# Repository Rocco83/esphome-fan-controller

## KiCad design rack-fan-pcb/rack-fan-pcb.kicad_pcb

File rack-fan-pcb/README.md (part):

# Rack fan controller board

Controller board for the rack's 19" fan tray: six 4-pin PWM fans, up to eight DS18B20 probes, wired Ethernet. KiCad 10 project, through-hole parts only, **manufactured PCB** (it started as a perfboard design).

- Firmware: [`../rack-fan.yaml`](../rack-fan.yaml) + [`../rack-fan-channel.yaml`](../rack-fan-channel.yaml)
- Project overview, fan choice and control logic: [`../README-rack-fan.md`](../README-rack-fan.md)
- This file: every decision taken for the board, why, and what the alternatives were.

## Contents

- [Summary](#summary)
- [Decisions](#decisions)
- [Pin assignment](#pin-assignment)
- [Board layout](#board-layout)
- [Parts](#parts)
- [Library sources](#library-sources)
- [Firmware coupling](#firmware-coupling)
- [Verification status](#verification-status)
- [Open items](#open-items)
- [Sources](#sources)

## Summary

| Area | Decision |
|---|---|
| Controller | WT32-ETH01 (ESP32 + LAN8720), **mounted face down** in two 1 × 12 female sockets |
| Fans | 6 channels (Noctua NF-F12 industrialPPC-24V-3000 planned), each with its own PWM and tach |
| PWM stage | 2N3904 open collector per fan: 4.7 kΩ base, 100 kΩ pull-down, inverting |
| Tach | Direct to a GPIO per fan, 10 kΩ pull-up to 3.3 V, hardware pulse counter |
| Probes | DS18B20 on two 1-Wire buses (GPIO5, GPIO17), 4 JST XH connectors per bus |
| Power in | 24 V, Mean Well GST90A24-P1M (5.5/2.5 jack J5), or an XLG LED driver on J1 |
| Protection | 5×20 T2A fuse (PTF78 holder), 1N5822 reverse-polarity diode, 470 µF bulk |
| Logic supply | Traco TSR 1-2450 (24 V → 5 V) into the WT32's 5V pin; 3.3 V from the WT32 |
| Boot robustness | C3 470 µF on EN; fans fail to 100% (except FAN1, see pin 26) |
| Board | Manufactured PCB, outline drawn by the user on Edge.Cuts (≈ 66.5 × 87 mm), parts on a 0.635 mm grid |
| Grounding | Star ground at the power input; logic ground enters the WT32 through **one** GND pin (WT32 GND and 3V3 pins declared as jumper groups) |
| Mounting | 4 × M3 holes (MountingHole_3.2mm_M3), 4 mm in from the corners, **not connected** |

## Decisions

### 1. Controller: WT32-ETH01, socketed, face down

- **Wired Ethernet** for a rack device: no Wi-Fi dependency.
- **Sockets:** the module plugs into two 1 × 12 female headers, so it can be removed to flash it over serial.
- **Pins 13 (LINK) and 14 (GND) have no socket.** They are the pair at the RJ45 end, and with the RJ45 overhanging the board they fall ~0.5 mm past the edge. The edge can't move out to include them: face down, the RJ45 body must clear the board, and it starts only ~1.7 mm beyond the edge. LINK was unused and pin 14 is one of five GND pins, so nothing is lost. The module's two pins simply hang beside the edge. The pads are removed from the footprint and the pins from the symbol; the other pins keep their numbers.
- **Face down:** the module sits components-towards-the-board. That mirrors its two pin rows, so the project uses its own footprint `rack-fan:WT32-ETH01_Socket_FaceDown`. The RJ45 overhangs the left board edge.
- **Row spacing:** 22.86 mm (9 holes), cross-checked against an independent KiCad footprint ([egnor/wt32-eth01](https://github.com/egnor/wt32-eth01)). Measure the module with calipers before soldering the sockets.
- **Pins left:** Ethernet takes GPIO0, 16, 18, 19, 21, 22, 23, 25, 26 and 27. Only 14 GPIOs remain on the header: 1, 2, 3, 4, 5, 12, 14, 15, 17, 32, 33, 35, 36, 39. That budget drives most of the decisions below.

### 2. Six fans, not eight

- 6 PWM + 6 tach + 2 probe buses use all 14 pins.
- **8 fans would need a tach multiplexer.** A 74HC4052 reads one fan at a time, so RPM would update only every ~10 s. Rejected: instant tach readings were preferred.
- **Other ways to 8 fans, both rejected:**
  - a second microcontroller counting the tachs and reporting over I2C
  - an I2C fan-controller chip (MAX31790, EMC2305), which is surface-mount and has no ESPHome support
- **PCA9685 (on hand): rejected.** Its PWM tops out at 1526 Hz (about 3 kHz with an external clock), and the fans need 21–28 kHz. Its I2C also costs 2 pins, and the PW package is surface-mount.

### 3. PWM stage: 2N3904 open collector

```
GPIO ──┬──[4.7 kΩ]── 2N3904 base           fan's internal pull-up
       │             collector ─────────────────┴── fan PWM wire (pin 4)
   [100 kΩ]          emitter ── GND
       │
      GND
```

Why it's needed:
- **Levels:** the fan pulls its PWM wire up to as much as 5 V, above the ESP32's 3.3 V rating, and 3.3 V does not reach the 4.75 V high threshold of some fans (San Ace).

Why this circuit:
- **Drive:** 3.3 V through 4.7 kΩ gives about 0.56 mA of base current. That saturates the transistor at 0.1–0.2 V for the ≤ 5 mA a fan input sinks, guaranteed at 3.3 V. At 25 kHz, turn-off delay costs about 1% of duty.
- **Inverting:** the firmware sets `inverted: true`, so the output level equals the fan duty.
- **Fail-safe:** GPIO low, floating or unpowered means the transistor is off, the wire floats high, and the fan runs at 100%.
- **Strapping pins:** the 100 kΩ pull-down keeps GPIO2 and GPIO12 low at boot.

Alternatives rejected:

| Alternative | Why not |
|---|---|
| 2N7000 MOSFET | Worst-case gate threshold 3 V, too close to the 3.3 V drive |
| 74LVC06A (open-drain inverter) | Surface-mount only |
| BSS138 level-shifter module | Its 3.3 V-side pull-up holds GPIO2/GPIO12 high at boot (GPIO12 high = no boot) |
| 74AHCT125 5 V buffer | Non-inverting: a dead GPIO stops the fan |
| TXB0108 / TXS0108 | Auto-direction shifters misbehave with the fans' pull-ups |
| ULN2003 / ULN2803 | Darlington saturation ~0.9 V, above the 0.4 V low threshold of some fans |
| Direct GPIO | Over-voltage on the pin; insufficient high level |
| 4.7 kΩ pull-downs on pins with a reset pull-up | Would make those fans fail-safe at boot, but rejected: no resistor value changes. Fixed instead by choosing which pins carry PWM (see pin assignment) |

### 4. Tach inputs: direct, one GPIO per fan

- **Circuit:** open collector, 2 pulses per revolution, one 10 kΩ pull-up per fan to **3.3 V** (never 5 V). The pull-up is required on GPIO35/36/39, which have no internal pull-up.
- **Counting:** a hardware pulse counter per fan (6 of the ESP32's 8), live RPM.
- **Filter:** `internal_filter: 13us` (the hardware maximum, 12.8 µs). It also removes the ~80 ns low glitches that ESP32 erratum GPIO-3.11 puts on GPIO36/39 when the ADC powers on. The firmware doesn't use the ADC; the filter is a safeguard.
- **Not on the module's LED pins:** the WT32 has LEDs on GPIO5 and GPIO17. As a tach input, the LED path would add up to ~1.5 mA, against the Noctua's 2 mA tach rating.

### 5. Temperature probes: DS18B20 on two 1-Wire buses

- **DS18B20 chosen over NTC (both on hand):**
  - NTCs need analog inputs, and the ADC1 pins (32/33/35/36/39) are all used.
  - An I2C ADC (ADS1115) would need 2 more pins.
  - The I2C multiplexer (also on hand) was for SHT21 probes sharing one address; DS18B20s share a bus without it.
- **Two buses, 4 connectors each, odd/even:** J21–J24 are TEMP1, 3, 5, 7 (bus A, ONEWIRE_A) and J25–J28 are TEMP2, 4, 6, 8 (bus B, ONEWIRE_B). The hot zone has probes on both buses, so a bus fault (crushed cable, shorted probe) still leaves a hot-zone reading; it also keeps each star of cables short.
  - Bus A: TEMP1 Rear High, TEMP3 Rear Low, TEMP5 Front Low, TEMP7 Inlet.
  - Bus B: TEMP2 Rear Mid, TEMP4 Front High, TEMP6 Outlet, TEMP8 Other Room.
- **Pins GPIO5 and GPIO17:** the module's LED3/LED4 sit there (3V3 → LED → 1 kΩ → pin). For 1-Wire that's harmless: about 1.3 mA of extra pull-up, well within the DS18B20's 4 mA sink, and the LEDs blink with traffic. Those pins were bad for PWM and tach, so 1-Wire is their best use.
- **Pull-up:** 4.7 kΩ per bus (R31, R32); use 2.2 kΩ for long cables.
- **Connectors:** JST XH 3-pin vertical (B3B-XH-A), pin order 1 GND, 2 DQ, 3 VDD.
  - 5.08 mm screw terminals were the first choice but **did not fit**: four in a row need ~17 holes plus spacing, and only ~18 were free beside the fan resistors.
  - XH needs a crimped plug on each probe cable.
- **Probes and names:** eight probes, named after their connector: TEMP1 Rear High, TEMP2 Rear Mid, TEMP3 Rear Low, TEMP4 Front High, TEMP5 Front Low, TEMP6 Outlet, TEMP7 Inlet, TEMP8 Other Room. Cables: 5 m on TEMP4, 6 and 8, 2 m on the others. ESPHome shows them as `Rack Fan TEMP1 Rear High` … `Rack Fan TEMP8 Other Room`. Each name is bound to a probe address in the firmware, so each probe must go into the connector of its name.

### 6. Power

**Input supply: Mean Well GST90A24-P1M** (24 V, 3.75 A, 90 W desktop adapter).
- True constant-voltage supply, and **no mains wiring** on the project at all.
- The **P1M plug is 5.5/2.5 mm, centre positive** (Mean Well datasheet), so J5 must be a **2.5 mm-pin** barrel jack. The common DC-005 jack comes in both pin sizes with the same body, so the footprint fits either.
- **No jack takes both 2.1 and 2.5 reliably.** A 2.1 pin accepts a 2.5 plug but with loose contact, which isn't acceptable at ~26 W. A 2.5 pin doesn't accept a 2.1 plug.
- In Italy, generic adapters are more often 5.5/2.1. If that's preferred, use the GST90A24-P1J with a 2.1 jack.
- **Alternatives:** Mean Well XLG-100-24-A or XLG-75-24-A LED drivers on **J1** (5.08 mm screw terminal). Below their current setting they act as a 24 V supply; leave the potentiometer at maximum. Their flying mains leads need an earthed enclosure wired by someone qualified. Fit J1 **or** J5, not both.

**Load:** 6 × 4.32 W ≈ 26 W (1.1 A) for the fans, plus ~1.5 W of logic.

On the board:

| Ref | Part | Why |
|---|---|---|
| F1 | 5×20 fuse **T2A** (slow-blow) in a Stelvio-Kontek PTF78 holder | Protects the wiring on a short. The footprint is the same one used in espfreezanz. It replaced an earlier resettable PTC fuse |
| D1 | 1N5822 Schottky (3 A) | Reverse polarity. Drops ~0.5 V, so the fans see ~23.5 V |
| C1 | 470 µF 35 V | Bulk capacitance on the fan rail: fan start-up and PWM current pulses |
| U2 | Traco TSR 1-2450 | 24 V → 5 V, 1 A, input 6.5–36 V, fixed output. Preferred to an LM2596 module, which is adjustable and can be set wrong, and has no grid-friendly footprint |
| C2 | 47 µF 10 V | TSR output capacitor |
| C3 | 470 µF 10 V on **EN** | Boot robustness, see below |

**3.3 V** for the pull-ups and probes comes from the WT32's own regulator (pin 10), well under 50 mA.

**C3 on EN, and why not a bigger capacitor on 24 V instead:**
- Some WT32-ETH01 boards hang at power-up when the supply ramps slowly. The ESP32 leaves reset while its 3.3 V is still rising (adapter → TSR → module regulator).
- A capacitor on EN holds the ESP32 in reset until the supply has settled. 470 µF is the value users reported fixing it, with ~1.5–2 s of extra boot delay ([WLED forum](https://wled.discourse.group/t/wt32-eth01-hangs-on-boot-after-psu-power-up/2937)).
- A bigger capacitor on the 24 V line would make the ramp **slower**, the condition that causes the hang. C1 stays for the fan rail; C3 is a different job.
- A smaller C3 (e.g. 100 µF) fits the same footprint and boots faster, but nobody has reported testing it.

### 7. Board type: manufactured PCB

The board started as a perfboard layout (Eurocard, everything on the 2.54 mm hole grid). It is now a **manufactured PCB**:
- The outline is the rectangle the user drew on Edge.Cuts, about 66.5 × 87 mm.
- Parts sit on a 0.635 mm (25 mil) placement grid instead of the 2.54 mm hole grid. That allows the tighter resistor packing and channel pitch below.

### 8. Grounding: star ground, one WT32 GND pin

- **The concern:** the WT32's five GND pins (2, 9, 11, 14, 23; 14 is not fitted) are all tied to the module's internal ground plane. Linking them again on the board only adds a small parallel path, which is harmless in itself. The real risk is the **fan return current** (up to ~1.1 A, pulsed at 25 kHz) entering the module at one GND pin and leaving at another. The ESP32 and the Ethernet PHY would then sit on a bouncing ground.
- **Decision: star ground** at the power input (J5/J1, C1):
  - **Power branch:** fan returns (J11–J16 pin 1), the 2N3904 emitters and the 100 kΩ pull-downs go straight to the star point.
  - **Logic branch:** WT32, TSR 1-2450 ground, C2, C3, the probe GND and R31/R32 go to the star point as their own branch. That branch enters the module through **one** GND pin.
  - Fan current then never crosses the module.
- **How KiCad accepts it:** the WT32 symbol and footprint declare **jumper groups**: GND (2, 9, 11, 23), 3V3 (3, 10). EN (1, 4) was a group too, but KiCad 10's *Update PCB from Schematic* then split the EN net in two (`/EN` on pin 1, `/EN_1` on pin 4 and its tracks), so it was removed: pin 1 carries a no-connect flag and pin 4 is the routed EN pin. The module ties them internally.
  - KiCad 9/10 then treats each group as connected inside the part, so routing one pin per group satisfies the ratsnest and DRC.
  - Tokens: `jumper_pin_groups` in the symbol, `jumper_pad_groups` in the footprint, as written by KiCad's own file formatter.
  - KiCad 10.0.4 bug #25063 affects only pins defined as a list, not this part.
- **Which GND pin:** route the logic branch to the WT32 GND pin nearest the 5V/3V3 pins (pin 9 or 11), so the module's supply and its return are next to each other.

### 9. Mounting holes

- **What:** 4 × stock `MountingHole:MountingHole_3.2mm_M3` (same footprint as espfreezanz), centres 4 mm in from each corner of the outline.
- **Not connected, deliberately.** Metal holes tied to GND would make the chassis a second ground path, a real ground loop.
- **No schematic symbol:** they are board-only footprints (H1–H4).

### 10. Serial

- UART0 (GPIO1/GPIO3) carries FAN1's PWM and tach, so **there is no serial console at runtime**. Logs come over the API and the web server.
- **Flashing:** over the network after the first flash. For a serial flash (first flash, or recovery) use the three headers below, or take the module out of its sockets.
- **J2 UART** (1 × 3, 2.54 mm): 1 GND, 2 RX = IO3/RXD0 (net TACH1), 3 TX = IO1/TXD0 (net PWM1). Labels are from the ESP32's side: the adapter's TX goes to pin 2, its RX to pin 3. Use a **3.3 V** adapter and **unplug FAN1** first, since its tach would drive RX. The PWM1 stage (4.7 kΩ into Q1's base, 100 kΩ pull-down) only loads TX lightly.
- **J3 RESET** (1 × 3): 1 EN, 2 GND, 3 not connected. A jumper on 1-2 holds the ESP32 in reset; pin 3 is the parking place (jumper on 2-3). Shorting EN also discharges C3 (470 µF) through the jumper, which is harmless at 3.3 V.
- **J4 BOOT** (1 × 3): 1 IO0, 2 GND, 3 not connected. Jumper on 1-2 at power-on (or while releasing RESET) = serial download mode; park it on 2-3 for normal use.
- **IO0 is the Ethernet 50 MHz clock input.** The track to J4 is a stub on that clock: keep it **as short as possible**, J4 right next to U1 pin 24, and never leave the BOOT jumper on in normal use. A long IO0 track can break Ethernet.
- **Flash procedure:** FAN1 unplugged, adapter on J2, BOOT jumper on 1-2, power on (or RESET jumper on 1-2 and off), flash, BOOT jumper back to 2-3, reset.
- **Placement:** J2–J4 were added outside the board outline (right side), with nets assigned; place and route them by hand.

## Pin assignment

### Rules that decide every pin

From the [ESP32 datasheet](https://www.espressif.com/sites/default/files/documentation/esp32_datasheet_en.pdf) (strapping pins, IO_MUX reset states) and the [WT32-ETH01 V1.4 schematic](https://github.com/egnor/wt32-eth01):

**Must-haves:**
- **GPIO12 (MTDI)** must be low at boot, or the flash gets 1.8 V and the board won't boot. It can only carry a pulled-down PWM.
- **GPIO2** must be low or floating to enter serial download mode. It can only carry a pulled-down PWM.
- **GPIO35/36/39** are input-only with no pull resistors, so they can only be tachs.
- **GPIO1 (U0TXD)** carries the ROM boot message and is pulled up at reset. It can't be a tach (driven at boot).
- **GPIO0** is the Ethernet clock: unusable.

**What makes a pin good or bad for a job:**
- **PWM is only fail-safe** on pins that are low or floating during reset: GPIO2, GPIO4, GPIO12 (internal pull-down) and GPIO32, GPIO33 (no pull). That's only **5 pins for 6 PWMs**. The 6th PWM necessarily sits on a pin that switches its fan off during reset and boot.
- **Pins with an internal pull-up at reset:** GPIO3, GPIO5, GPIO14, GPIO15 (and GPIO1). Harmless for a tach or 1-Wire; for PWM, the fan stops while the ESP32 is in reset.
- **Module LED pins (GPIO5, GPIO17):** good for 1-Wire. Tight for a tach (current), not fail-safe for PWM.
- **Routing:** the face-down mount swaps the rows. Assignments were chosen to keep each signal on the row nearest its destination, to avoid crossings between the two rows.

### Final assignment

Pins 14–26 are one header row, 1–13 the other. "Pin" is the WT32 header pin, which is also the footprint pad.

| Pin | GPIO | Function | Why this pin | Alternatives for this pin | Caveat |
|---|---|---|---|---|---|
| 26 | IO1 | **PWM1** | Closest pin to FAN1. It couldn't be a tach, and moving 1-Wire to the LED pins freed it | 1-Wire. Not a tach | FAN1 stops for ~1 s at each boot/OTA reboot (reset pull-up, ROM message, then idle high until `on_boot` sets 100%), and stays stopped if the ESP32 is stuck rebooting or held in reset. Accepted: the 6th PWM has to be on such a pin |
| 25 | IO3 | **TACH1** | Pull-up at reset = tach idle level. RX is unused at runtime | PWM (fan would stop during reset), 1-Wire | None |
| 24 | IO0 | **BOOT (J4)** | Ethernet clock input; strapping pin (low = download mode) | — | Only a very short track to J4 |
| 23 | — | GND | | | |
| 22 | IO39 | **TACH2** | Input-only: tach is the only use | Another tach only | Erratum GPIO-3.11 glitch removed by the filter |
| 21 | IO36 | **TACH3** | Input-only: tach is the only use | Another tach only | Erratum GPIO-3.11 glitch removed by the filter |
| 20 | IO15 | **TACH4** | Strapping pin (boot log) whose default is high; the tach pull-up keeps it there | 1-Wire. PWM would stop its fan during reset (pull-up) and silence the boot log | Hobby sources claim a short pulse burst at boot; Espressif documents output disabled (see open items) |
| 19 | IO14 | **TACH5** | Pull-up after reset = tach idle level | 1-Wire. PWM would stop its fan during reset | Same undocumented boot-burst claim |
| 18 | IO12 | **PWM2** | Must stay low at boot: only a pulled-down PWM qualifies | Another PWM only. Never a tach or 1-Wire (pull-up → no boot) | None while the 100 kΩ pull-down is fitted |
| 17 | IO35 | **TACH6** | Input-only: tach is the only use | Another tach only | None |
| 16 | IO4 | **PWM3** | Pull-down at reset: fail-safe PWM | Tach, 1-Wire | None |
| 15 | IO2 | **PWM4** | Must stay low/floating for serial download: only a pulled-down PWM qualifies. Pull-down at reset: fail-safe | Another PWM only. Never a tach or 1-Wire | None |
| 14 | — | GND (no socket) | | | Past the board edge, not fitted |
| 1 | EN | — | Same signal as pin 4 | | Unconnected |
| 2 | — | GND | | | |
| 3 | 3V3 | — | Same rail as pin 10 | | Unconnected |
| 4 | EN | **EN** | C3 to GND | | Adds ~1.5–2 s of boot delay |
| 5 | IO32 | **PWM6** | No pull at reset: fail-safe PWM | Tach, 1-Wire | None (v2: swapped with PWM5 for routing) |
| 6 | IO33 | **PWM5** | No pull at reset: fail-safe PWM | Tach, 1-Wire | None (v2: swapped with PWM6 for routing) |
| 7 | IO5 | **ONEWIRE_A** | Module LED3: the best use is 1-Wire. Strapping pin whose default is high, kept by the bus pull-up | Tach (tight: LED current against the 2 mA tach rating). PWM would stop its fan during reset (pull-up + LED) | LED3 blinks with bus traffic |
| 8 | IO17 | **ONEWIRE_B** | Module LED4: the best use is 1-Wire | Tach (tight, as above). PWM would stop its fan during reset (LED pull-up) | LED4 blinks with bus traffic |
| 9 | — | GND | | | |
| 10 | 3V3 | **3.3V** | Supply for pull-ups and probes | | < 50 mA |
| 11 | — | GND | | | |
| 12 | 5V | **+5V** | From U2 (TSR 1-2450) | | |
| 13 | LINK | — (no socket) | | | Past the board edge, not fitted |

Result:
- Every fan except FAN1 runs at 100% from power-on until the firmware takes over, and if the ESP32 is in reset.
- There's no strapping conflict.
- The module LEDs only blink on the probe buses.

**How the assignment evolved**, for the record:
1. **First pass:** probe buses on GPIO1/GPIO3, tachs partly on GPIO5/GPIO17.
2. **Second pass:** after the module was turned face down, the assignment was rearranged for routing. FAN5/FAN6 went to the short row, and each fan's PWM and tach went on the row nearest its connector.
3. **Final:** the reset-state analysis and the WT32 schematic (LEDs on GPIO5/GPIO17) moved 1-Wire to the LED pins and the pull-up pins (IO3, IO14, IO15) to tachs. That left only the unavoidable 6th PWM on GPIO1, which is closest to FAN1. A swap of ONEWIRE_B onto GPIO14 was considered and dropped, because it moved signals between rows.

## Board layout

- **Outline:** the user's Edge.Cuts rectangle (≈ 66.5 × 87 mm).
  - The fan headers sit on the right edge.
  - The RJ45 overhangs the left edge on purpose.
  - The barrel jack J5 extends past the top edge (see open items).
- **Grid:** 0.635 mm (25 mil) placement grid. The part's pin 1 is on the grid; pins with their own pitch (XH 2.50 mm, fuse holder 22.6 mm, C1 5.00 mm) follow from it.
- **Fan channels:** one column, **FAN1 at the top of the board**, pitch **11.43 mm**. The fan header's housing is 11.1 mm, so they don't touch. Every channel copies the user-defined channel-6 pattern, aligned:
  - **fan header** (pad 1 at the top: GND, +24V, TACH, PWM)
  - **2N3904** to its left, its **bottom pin (collector) level with the fan header's bottom pin (PWM)**
  - **three resistors packed together** to the left, rows **3.175 mm** apart (0207 courtyard 3.0 mm, so no overlaps), the bottom row level with the fan header's bottom pin:
    - 100 kΩ pull-down (top)
    - 4.7 kΩ base (middle)
    - 10 kΩ tach pull-up (bottom)
  - the three resistors share one column (pad 1 x), the transistors another, the fan headers another
- **TEMP1–TEMP8 (JST XH):** two rows of four at equal spacing (9.525 mm), rows 12.07 mm apart, bottom-left.
- **R32, R31, C3:** one row under the WT32. C3 sits just clear of the module outline.
- **Power:** top-left (J1/J5, F1, D1, C1, U2, C2), snapped to the grid without changing the user's arrangement.
- **Silkscreen:**
  - connectors show their function: FAN1–FAN6, TEMP1–TEMP8, 24V IN
  - **back silkscreen (B.SilkS, mirrored):**
    - **the value of every part:** resistors, capacitors, Q1–Q6 (2N3904), D1, U1, U2 and F1. For F1 and the connectors, whose value is printed on the front, it's a board text copy, so their footprints still match the library.
    - **the use of every connector pin:** FAN1–FAN6 GND / +24V / TACH / PWM; TEMP1–TEMP8 GND / DQ / 3V3; J1 + / GND.
    - checked: no back text overlaps another, a pad or the board edge
    - pin labels are 0.7 mm high, values 0.8 mm. The board's minimum text height rule is set to **0.7 mm** to match (it was 0.8 mm). Check that your fab accepts 0.7 mm silkscreen text; if not, enlarge the pin labels instead.
  - reference designators are on the fabrication layer
  - "LOW" (above FAN1) and "HIGH" (below FAN6) mark the zones, so the tray is mounted with FAN1 at the bottom
- **Tracks:** routed by the user (238 segments, both layers). KiCad 10 DRC: no errors, warnings only.
- **Net classes** (project file):

  | Class | Nets | Track | Clearance | Why |
  |---|---|---|---|---|
  | Power | +24V, GND, VIN_RAW, VIN_FUSED | 1.0 mm | 0.2 mm | ~1.1 A of fan current (6 × 0.18 A), more under a fault before the T2A fuse opens. 1.0 mm on 1 oz copper carries ~2.4 A at 10 °C rise (IPC-2221); 0.2 mm would run ~24 °C warmer at 1.1 A |
  | Supply_5V | +5V | 0.5 mm | 0.2 mm | WT32 supply, ~0.3 A |
  | Default | everything else | 0.2 mm | 0.2 mm | Signals, 3.3 V (< 50 mA) |

- **Existing tracks were widened** to their class width where clearance allows. Clearance stays ≥ 0.2 mm and the edge distance ≥ 0.5 mm:
  - **1.0 mm:** 41 GND and 19 +24V segments, and all VIN_RAW/VIN_FUSED.
  - **0.5 mm:** the per-fan +24V branches (0.18 A each, fine).
  - **0.2–0.5 mm:** the probe-side GND, which carries only milliamps, and part of +5V. Both are fine.
- **Three GND bottlenecks** on the fan return path still need a small reroute (see open items).

## Parts

| Ref | Value / part | Footprint |
|---|---|---|
| U1 | WT32-ETH01, face down, 2 × 1×12 female sockets (no 13/14) | `rack-fan:WT32-ETH01_Socket_FaceDown` |
| U2 | Traco TSR 1-2450 | `Converter_DCDC:Converter_DCDC_TRACO_TSR-1_THT` |
| J1 | 24V IN screw terminal (XLG option) | `TerminalBlock_Phoenix:…MKDS-1,5-2-5.08…` |
| J5 | 24V IN barrel jack 5.5/2.5 (GST90A24-P1M), pin 3 = switch, unused | `Connector_BarrelJack:BarrelJack_Horizontal` |
| F1 | Fuse T2A 5×20 + PTF78 holder | `Fuse:Fuseholder_Cylinder-5x20mm_Stelvio-Kontek_PTF78_Horizontal_Open` |
| D1 | 1N5822 | `Diode_THT:D_DO-201AD_P12.70mm_Horizontal` |
| C1 | 470 µF 35 V | `Capacitor_THT:CP_Radial_D10.0mm_P5.00mm` |
| C2 | 47 µF 10 V | `Capacitor_THT:CP_Radial_D5.0mm_P2.50mm` |
| C3 | 470 µF 10 V | `Capacitor_THT:CP_Radial_D6.3mm_P2.50mm` |
| J11–J16 | FAN1–FAN6, 4-pin PWM fan header | `Connector:FanPinHeader_1x04_P2.54mm_Vertical` |
| Q1–Q6 | 2N3904 | `Package_TO_SOT_THT:TO-92_Inline_Wide` |
| R1–R6 | 4.7 kΩ (base) | `Resistor_THT:R_Axial_DIN0207_L6.3mm_D2.5mm_P7.62mm_Horizontal` |
| R11–R16 | 100 kΩ (pull-down) | same |
| R21–R26 | 10 kΩ (tach pull-up) | same |
| R31, R32 | 4.7 kΩ (1-Wire pull-ups, bus A/B) | same |
| J2–J4 | UART, RESET, BOOT: 1 × 3 pin headers | `Connector_PinHeader_2.54mm:PinHeader_1x03_P2.54mm_Vertical` |
| J21–J28 | TEMP1, 3, 5, 7, 2, 4, 6, 8 (odd bus A, even bus B), JST XH 3-pin (B3B-XH-A) | `Connector_JST:JST_XH_B3B-XH-A_1x03_P2.50mm_Vertical` |
| H1–H4 | M3 mounting holes, not connected (board-only) | `MountingHole:MountingHole_3.2mm_M3` |

Off the board: the fans, the GST90A24-P1M, the DS18B20 probes with JST XHP-3 plugs, a 3.3 V USB-serial adapter for the first flash. The full BOM with order status is in [`../README-rack-fan.md`](../README-rack-fan.md#bill-of-materials).

## Library sources

Every symbol and footprint comes from the **stock KiCad libraries**, with one exception:

| Ref | Library item | Stock? |
|---|---|---|
| **U1** | symbol `rack-fan:WT32-ETH01`, footprint `rack-fan:WT32-ETH01_Socket_FaceDown` | ⚠️ **No.** KiCad's official libraries have no WT32-ETH01, checked in the current kicad-symbols and kicad-footprints repositories (`RF_Module`). Both items live in this project's own library (`rack-fan.kicad_sym`, `rack-fan.pretty/`), shipped with the project. The pad layout was cross-checked against an independent footprint (egnor/wt32-eth01) |
| All other parts | `Device`, `Connector`, `Connector_Generic`, `Motor`, `Diode`, `Regulator_Switching`, `Transistor_BJT`, `power` symbols; `Capacitor_THT`, `Connector`, `Connector_BarrelJack`, `Connector_JST`, `Converter_DCDC`, `Diode_THT`, `Fuse`, `MountingHole`, `Package_TO_SOT_THT`, `Resistor_THT`, `TerminalBlock_Phoenix` footprints | Yes |

How the check was done:
- Every library item was compared against the stock libraries shipped with KiCad 9.0.2. All items exist there under the same names.
- KiCad 10 keeps these libraries, but if KiCad 10 reports a missing library item when opening the project, that's the place to look.

**Symbols changed to match the parts** (footprints, pin numbers and nets unchanged):
- J5: `Connector:Barrel_Jack` → `Connector:Barrel_Jack_Switch`, so the symbol has the footprint's third pad (switch contact, not connected).
- J21–J28: `Connector:Screw_Terminal_01x03` → `Connector_Generic:Conn_01x03`, since they're XH headers now.
- J11–J16: `Connector_Generic:Conn_01x04` → `Motor:Fan_4pin`, which shows the fan with pins −, +, Tacho, PWM.

**U1 stays custom (decision):** the project's own symbol and footprint keep the module outline, the pin names and single-part placement.

**Stock alternative for U1 (not applied):** two `Connector_Generic:Conn_01x13` symbols on `Connector_PinSocket_2.54mm:PinSocket_1x13_P2.54mm_Vertical` footprints, placed 22.86 mm apart and mirrored for the face-down mount. That would make the project 100% stock, at the cost of the outline, pin names and single-part placement.

## Firmware coupling

- **Target:** the latest ESPHome (2026.10.1) on the **ESP-IDF** framework. Compiled successfully; not yet run on hardware.
- **Pin map:** matches the table above. The `packages:` entries in `rack-fan.yaml` carry a comment with the WT32 pin numbers.

Workarounds the board relies on:
- **`on_boot` (priority 700):** all fans to 100% immediately. ESPHome creates the LEDC outputs at level 0, which with `inverted: true` switches the transistors on and would stop every fan until the first control update.
- **`CONFIG_ESP_CONSOLE_NONE` and `CONFIG_BOOTLOADER_LOG_LEVEL_NONE`:** keep ESP-IDF's messages off GPIO1 (FAN1's PWM). Only the short ROM boot message remains, because pin 20 holds the strapping pin high.
- **`logger: baud_rate: 0`:** UART0 is used by FAN1.
- **`internal_filter: 13us`** on every tach.
- **Strapping warnings:** `ignore_strapping_warning` on GPIO2/12 (PWM), GPIO15 (tach) and GPIO5 (1-Wire). The ESPHome warning on GPIO0 is the Ethernet clock: expected.

## Verification status

**Done:**
- Every pin against the ESP32 datasheet (strapping, IO_MUX reset states), errata and the WT32-ETH01 V1.4 schematic.
- Schematic and board agree on all 150 pins, with zero mismatches.
- No shorts; minimum clearance 0.2 mm (project rule) after widening; tracks ≥ 0.5 mm from the edge.
- KiCad 10 DRC run by the user: no errors, warnings only (before widening).
- **Library match:** J1 and F1 graphics replaced with the KiCad 10.0.8 library versions (fixes the DRC warning "does not match copy in library"). Pads, nets and positions are unchanged.
- **Courtyard overlaps:** only the 4 mounting holes against parts at the corners (see open items). The resistor overlaps are gone with the 3.175 mm packing.
- **Outline:** U1's RJ45 overhangs the left edge on purpose. J5 extends past the top edge.
- **WT32 jumper groups:** present in the schematic, the board and both project-library files.
- Firmware validated and compiled with ESPHome 2026.10.1 / ESP-IDF.

**Not done here:**
- **KiCad's own ERC and DRC.** The files were edited as text from a machine with KiCad 9, which can't open KiCad 10 files. Run both in KiCad 10 after opening.
- **Hardware test.**

## Open items

### Backlog: board v2 and test harness

**What happened (2026-11):** two WT32-ETH01 modules died **on the same board** (power LED on, no Ethernet, ESP32 hot); the first while the board was only partly assembled. The second one died while a connector was being inserted with the board powered; the fans went to 100% at that moment (fail-safe of a dead ESP32). The board's nets are correct. Most likely cause: +24 V (fan header pin 2) touching TACH (pin 3), which goes **straight to a GPIO**: the 10 kΩ is a pull-up to 3.3 V, not a series resistor. An ESD discharge while touching the board is the other candidate. Until v2: never touch the board or plug connectors while it is powered. Board checked with no module fitted, 6 fans connected and powered: 3.3 V net floating (0.1–0.3 V, no source on the board), TACH 0 V, 20 kΩ between TACH nets (2 × 10 kΩ pull-ups) as expected, 24 V–5 V > 100 kΩ. The 3.5–4 V first read as "TACH" was the PWM line: the fan pulls its PWM input up internally, and that line only reaches the 2N3904 collector, not the ESP32. So the board puts no dangerous voltage on the module; the cause was a transient while handling the live board.

**v2 changes:**
- **TACH (×6), in the schematic:** 10 kΩ pull-up on the connector side (net `TACHn`), **22 kΩ series resistor R41–R46** to the GPIO (net `TACHn_IO`). With 24 V on TACH, under 1 mA reaches the pin. Optional, not drawn: clamp diode (1N4148) to 3.3 V. J2's RX stays on the GPIO side (`TACH1_IO`), so serial flashing doesn't go through the 22 kΩ.
- **1-Wire DQ (×2), in the schematic:** **220 Ω series resistor R47 (bus A), R48 (bus B)** between the bus (`ONEWIRE_A/B`, with its pull-up) and the GPIO (`ONEWIRE_A/B_IO`), against ESD from the long probe cables.
- **PCB:** run *Update PCB from Schematic* (F8): it adds R41–R48, TH1, JP1 and D2 (unplaced), moves D1's anode to `VIN_NTC`, and moves U1's TACH/1-Wire pads and J2 pin 2 to the `_IO` nets. The existing tracks from those U1 pads then need rerouting through the new resistors.
- **5 V rail:** 5.6 V zener / TVS.
- **24 V input, in the schematic:** **TH1**, NTC 5 Ω cold, ≥ 2 A (e.g. 5D-9, disc 9 mm, 5 mm pitch) in series between F1 and D1 (new net `VIN_NTC`), against the spark when the jack is plugged into a live supply (C1 470 µF charging). It only limits when cold. **JP1** (1 × 3 pin header, `BYPASS TH1`: 1 VIN_FUSED, 2 VIN_NTC, 3 not connected) sits in parallel: cap on 1-2 shorts TH1, so the board also works without TH1; cap on 2-3 is the parking position (NTC active). The cap carries the full 24 V current (~1.2 A). **D2**, P6KE30CA bidirectional TVS (DO-15) across +24 V / GND, against overshoot; bidirectional, so it can't go in the wrong way. Meanwhile: plug the jack first, then the supply into the mains.
- **Rail indicator LEDs, in the schematic:** D3 (red, +24V, R51 10 kΩ), D4 (yellow, +5V, R52 1.5 kΩ), D5 (green, +3V3, R53 680 Ω), each rail → resistor → LED → GND at about 2 mA. 3 mm THT LEDs (`LED_THT:LED_D3.0mm`, pin 1 = cathode, square pad). Not yet on the PCB: F8 adds them unplaced.
- **Fan headers:** keyed (Molex 47053 style), so a plug can't go in reversed or shifted.
- Space: 8 more 0207 resistors.
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
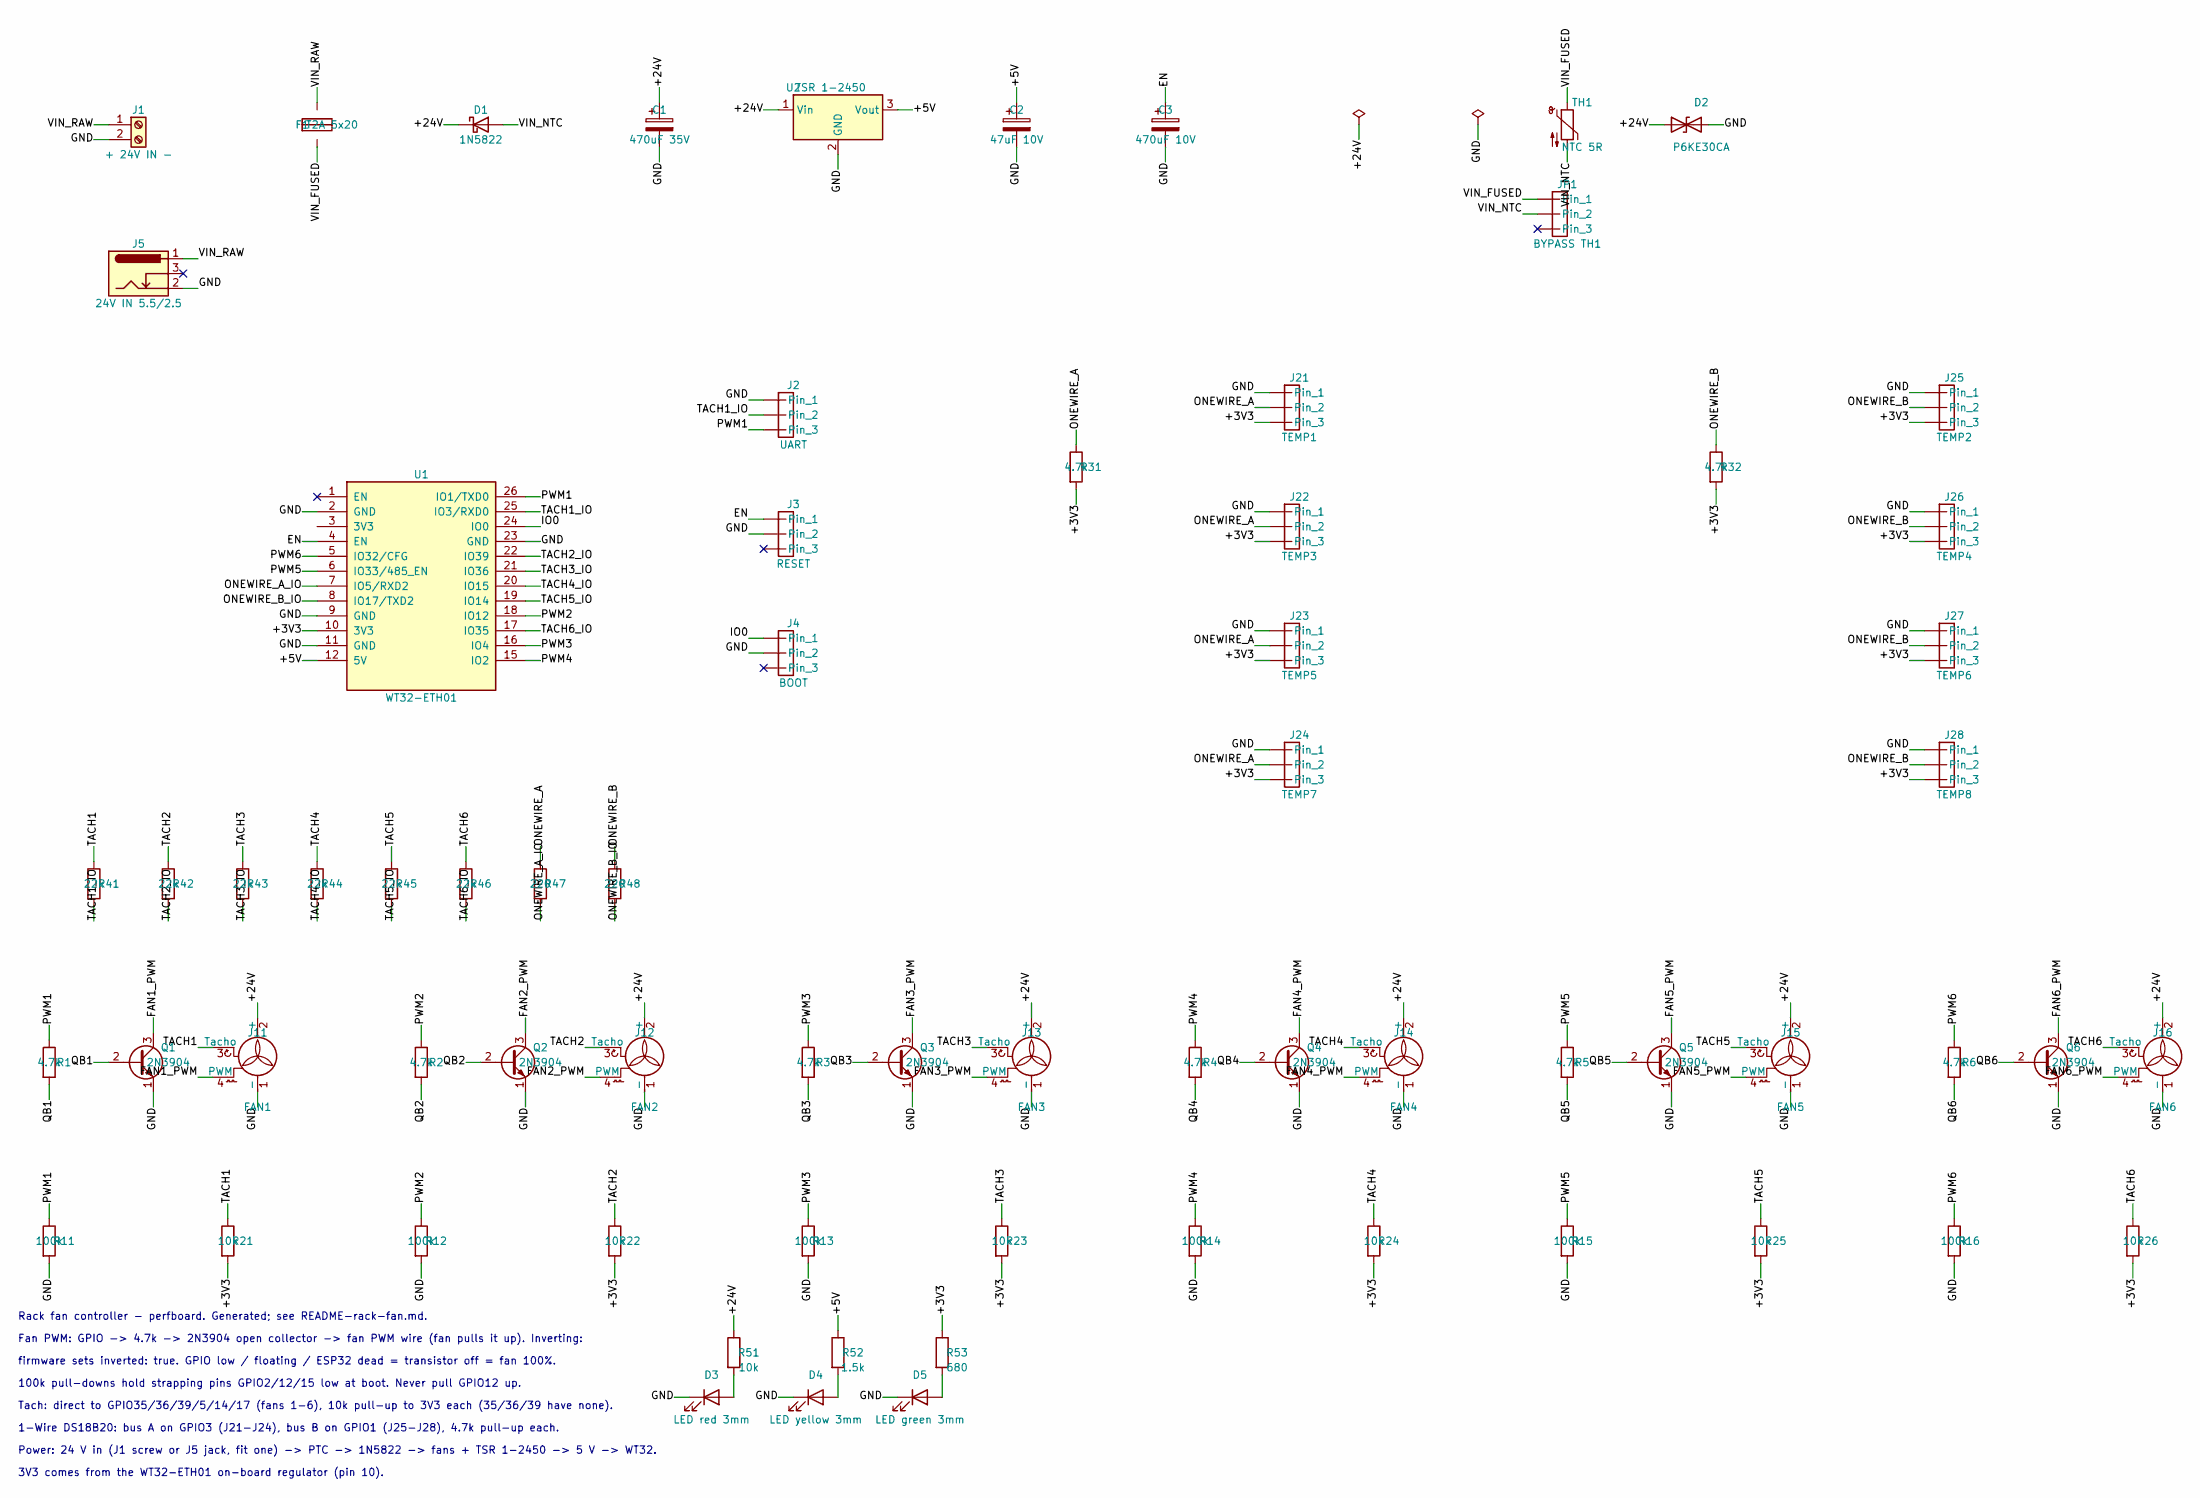
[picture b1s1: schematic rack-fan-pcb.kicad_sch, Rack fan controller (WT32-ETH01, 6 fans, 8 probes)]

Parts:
C1: 470uF 35V; CP_Radial_D10.0mm_P5.00mm
C2: 47uF 10V; CP_Radial_D5.0mm_P2.50mm
C3: 470uF 10V; CP_Radial_D6.3mm_P2.50mm
D1: 1N5822; D_DO-201AD_P12.70mm_Horizontal
D2: P6KE30CA; D_DO-15_P10.16mm_Horizontal
D3: LED red 3mm; LED_D3.0mm
D4: LED yellow 3mm; LED_D3.0mm
D5: LED green 3mm; LED_D3.0mm
F1: T2A 5x20; Fuseholder_Cylinder-5x20mm_Stelvio-Kontek_PTF78_Horizontal_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
J1: + 24V IN -; TerminalBlock_Phoenix_MKDS-1,5-2-5.08_1x02_P5.08mm_Horizont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
J2: UART; PinHeader_1x03_P2.54mm_Vertical
J3: RESET; PinHeader_1x03_P2.54mm_Vertical
J4: BOOT; PinHeader_1x03_P2.54mm_Vertical
J5: 24V IN 5.5/2.5; BarrelJack_Horizontal
J11: FAN1; FanPinHeader_1x04_P2.54mm_Vertical
J12: FAN2; FanPinHeader_1x04_P2.54mm_Vertical
J13: FAN3; FanPinHeader_1x04_P2.54mm_Vertical
J14: FAN4; FanPinHeader_1x04_P2.54mm_Vertical
J15: FAN5; FanPinHeader_1x04_P2.54mm_Vertical
J16: FAN6; FanPinHeader_1x04_P2.54mm_Vertical
J21: TEMP1; JST_XH_B3B-XH-A_1x03_P2.50mm_Vertical
J22: TEMP3; JST_XH_B3B-XH-A_1x03_P2.50mm_Vertical
J23: TEMP5; JST_XH_B3B-XH-A_1x03_P2.50mm_Vertical
J24: TEMP7; JST_XH_B3B-XH-A_1x03_P2.50mm_Vertical
J25: TEMP2; JST_XH_B3B-XH-A_1x03_P2.50mm_Vertical
J26: TEMP4; JST_XH_B3B-XH-A_1x03_P2.50mm_Vertical
J27: TEMP6; JST_XH_B3B-XH-A_1x03_P2.50mm_Vertical
J28: TEMP8; JST_XH_B3B-XH-A_1x03_P2.50mm_Vertical
JP1: BYPASS TH1; PinHeader_1x03_P2.54mm_Vertical
Q1, Q2, Q3, Q4, Q5, Q6: 2N3904; TO-92_Inline_Wide
R1, R2, R3, R4, R5, R6, R31, R32: 4.7k; R_Axial_DIN0207_L6.3mm_D2.5mm_P7.62mm_Horizontal
R11, R12, R13, R14, R15, R16: 100k; R_Axial_DIN0207_L6.3mm_D2.5mm_P7.62mm_Horizontal
R21, R22, R23, R24, R25, R26, R51: 10k; R_Axial_DIN0207_L6.3mm_D2.5mm_P7.62mm_Horizontal
R41, R42, R43, R44, R45, R46: 22k; R_Axial_DIN0207_L6.3mm_D2.5mm_P7.62mm_Horizontal
R47, R48: 220; R_Axial_DIN0207_L6.3mm_D2.5mm_P7.62mm_Horizontal
R52: 1.5k; R_Axial_DIN0207_L6.3mm_D2.5mm_P7.62mm_Horizontal
R53: 680; R_Axial_DIN0207_L6.3mm_D2.5mm_P7.62mm_Horizontal
TH1: NTC 5R; RV_Disc_D9mm_W5.2mm_P5mm
U1: WT32-ETH01; WT32-ETH01_Socket_FaceDown
U2: TSR 1-2450; Converter_DCDC_TRACO_TSR-1_THT

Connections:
/+3V3: J21.3, J22.3, J23.3, J24.3, J25.3, J26.3, J27.3, J28.3, R21.2, R22.2, R23.2, R24.2, R25.2, R26.2, R31.2, R32.2, R53.1, U1.3 (3V3), U1.10 (3V3)
/+5V: C2.1, R52.1, U1.12 (5V), U2.3 (Vout)
/+24V: C1.1, D1.1 (K), D2.1 (A1), J11.2 (+), J12.2 (+), J13.2 (+), J14.2 (+), J15.2 (+), J16.2 (+), R51.1, U2.1 (Vin)
/EN: C3.1, J3.1, U1.4 (EN)
/FAN1_PWM: J11.4 (PWM), Q1.3 (C)
/FAN2_PWM: J12.4 (PWM), Q2.3 (C)
/FAN3_PWM: J13.4 (PWM), Q3.3 (C)
/FAN4_PWM: J14.4 (PWM), Q4.3 (C)
/FAN5_PWM: J15.4 (PWM), Q5.3 (C)
/FAN6_PWM: J16.4 (PWM), Q6.3 (C)
/GND: C1.2, C2.2, C3.2, D2.2 (A2), D3.1 (K), D4.1 (K), D5.1 (K), J1.2, J2.1, J3.2, J4.2, J5.2, J11.1 (-), J12.1 (-), J13.1 (-), J14.1 (-), J15.1 (-), J16.1 (-), J21.1, J22.1, J23.1, J24.1, J25.1, J26.1, J27.1, J28.1, Q1.1 (E), Q2.1 (E), Q3.1 (E), Q4.1 (E), Q5.1 (E), Q6.1 (E), R11.2, R12.2, R13.2, R14.2, R15.2, R16.2, U1.2 (GND), U1.9 (GND), U1.11 (GND), U1.23 (GND), U2.2 (GND)
/IO0: J4.1, U1.24 (IO0)
/ONEWIRE_A: J21.2, J22.2, J23.2, J24.2, R31.1, R47.1
/ONEWIRE_A_IO: R47.2, U1.7 (IO5/RXD2)
/ONEWIRE_B: J25.2, J26.2, J27.2, J28.2, R32.1, R48.1
/ONEWIRE_B_IO: R48.2, U1.8 (IO17/TXD2)
/PWM1: J2.3, R1.1, R11.1, U1.26 (IO1/TXD0)
/PWM2: R2.1, R12.1, U1.18 (IO12)
/PWM3: R3.1, R13.1, U1.16 (IO4)
/PWM4: R4.1, R14.1, U1.15 (IO2)
/PWM5: R5.1, R15.1, U1.6 (IO33/485_EN)
/PWM6: R6.1, R16.1, U1.5 (IO32/CFG)
/QB1: Q1.2 (B), R1.2
/QB2: Q2.2 (B), R2.2
/QB3: Q3.2 (B), R3.2
/QB4: Q4.2 (B), R4.2
/QB5: Q5.2 (B), R5.2
/QB6: Q6.2 (B), R6.2
/TACH1: J11.3 (Tacho), R21.1, R41.1
/TACH1_IO: J2.2, R41.2, U1.25 (IO3/RXD0)
/TACH2: J12.3 (Tacho), R22.1, R42.1
/TACH2_IO: R42.2, U1.22 (IO39)
/TACH3: J13.3 (Tacho), R23.1, R43.1
/TACH3_IO: R43.2, U1.21 (IO36)
/TACH4: J14.3 (Tacho), R24.1, R44.1
/TACH4_IO: R44.2, U1.20 (IO15)
/TACH5: J15.3 (Tacho), R25.1, R45.1
/TACH5_IO: R45.2, U1.19 (IO14)
/TACH6: J16.3 (Tacho), R26.1, R46.1
/TACH6_IO: R46.2, U1.17 (IO35)
/VIN_FUSED: F1.2, JP1.1, TH1.1
/VIN_NTC: D1.2 (A), JP1.2, TH1.2
/VIN_RAW: F1.1, J1.1, J5.1
unnamed: D3.2 (A), R51.2
unnamed: D4.2 (A), R52.2
unnamed: D5.2 (A), R53.2

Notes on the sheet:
Tach: direct to GPIO35/36/39/5/14/17 (fans 1-6), 10k pull-up to 3V3 each (35/36/39 have none).
firmware sets inverted: true. GPIO low / floating / ESP32 dead = transistor off = fan 100%.
1-Wire DS18B20: bus A on GPIO3 (J21-J24), bus B on GPIO1 (J25-J28), 4.7k pull-up each.
Rack fan controller - perfboard. Generated; see README-rack-fan.md.
100k pull-downs hold strapping pins GPIO2/12/15 low at boot. Never pull GPIO12 up.
Fan PWM: GPIO -> 4.7k -> 2N3904 open collector -> fan PWM wire (fan pulls it up). Inverting:
3V3 comes from the WT32-ETH01 on-board regulator (pin 10).
Power: 24 V in (J1 screw or J5 jack, fit one) -> PTC -> 1N5822 -> fans + TSR 1-2450 -> 5 V -> WT32.

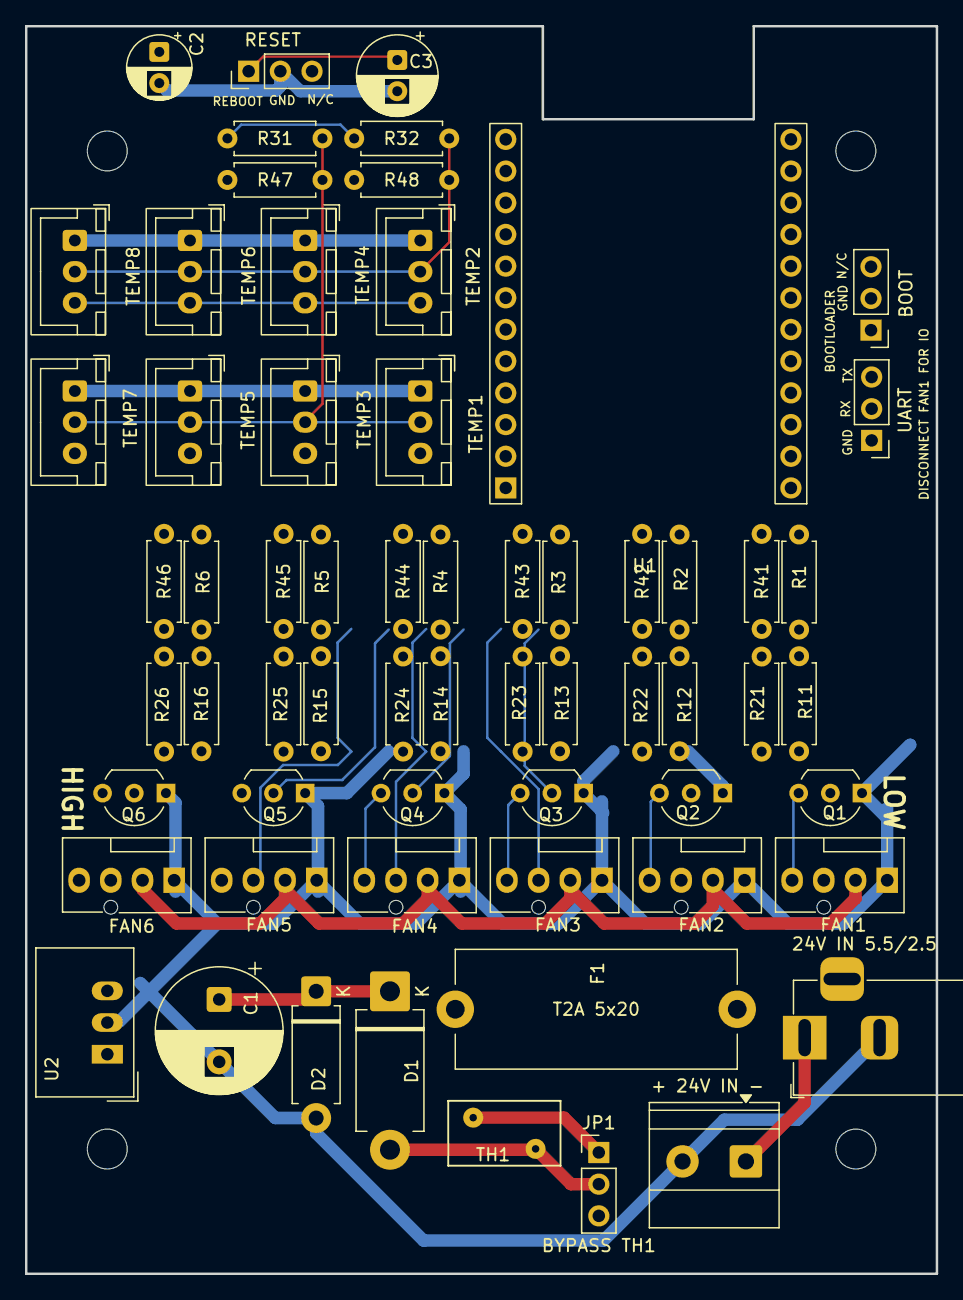
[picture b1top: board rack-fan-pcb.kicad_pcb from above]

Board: 2 copper layers, 73.0 x 100.0 mm, 67 parts (0 on the bottom side), 43 nets.

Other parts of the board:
H1, H2, H3, H4: M3; MountingHole_3.2mm_M3

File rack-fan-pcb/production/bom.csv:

Designator,Footprint,Quantity,Value,LCSC Part #
C1,CP_Radial_D10.0mm_P5.00mm,1,470uF 35V,
C2,CP_Radial_D5.0mm_P2.50mm,1,47uF 10V,
C3,CP_Radial_D6.3mm_P2.50mm,1,470uF 10V,
D1,D_DO-201AD_P12.70mm_Horizontal,1,1N5822,
F1,Fuseholder_Cylinder-5x20mm_Stelvio-Kontek_PTF78_Horizontal_Open,1,T2A 5x20,
J1,"TerminalBlock_Phoenix_MKDS-1,5-2-5.08_1x02_P5.08mm_Horizontal",1,+ 24V IN -,
J11,FanPinHeader_1x04_P2.54mm_Vertical,1,FAN1,
J12,FanPinHeader_1x04_P2.54mm_Vertical,1,FAN2,
J13,FanPinHeader_1x04_P2.54mm_Vertical,1,FAN3,
J14,FanPinHeader_1x04_P2.54mm_Vertical,1,FAN4,
J15,FanPinHeader_1x04_P2.54mm_Vertical,1,FAN5,
J16,FanPinHeader_1x04_P2.54mm_Vertical,1,FAN6,
J2,PinHeader_1x03_P2.54mm_Vertical,1,UART,
J21,JST_XH_B3B-XH-A_1x03_P2.50mm_Vertical,1,TEMP1,
J22,JST_XH_B3B-XH-A_1x03_P2.50mm_Vertical,1,TEMP3,
J23,JST_XH_B3B-XH-A_1x03_P2.50mm_Vertical,1,TEMP5,
J24,JST_XH_B3B-XH-A_1x03_P2.50mm_Vertical,1,TEMP7,
J25,JST_XH_B3B-XH-A_1x03_P2.50mm_Vertical,1,TEMP2,
J26,JST_XH_B3B-XH-A_1x03_P2.50mm_Vertical,1,TEMP4,
J27,JST_XH_B3B-XH-A_1x03_P2.50mm_Vertical,1,TEMP6,
J28,JST_XH_B3B-XH-A_1x03_P2.50mm_Vertical,1,TEMP8,
J3,PinHeader_1x03_P2.54mm_Vertical,1,RESET,
J4,PinHeader_1x03_P2.54mm_Vertical,1,BOOT,
J5,BarrelJack_Horizontal,1,24V IN 5.5/2.5,
"Q1, Q2, Q3, Q4, Q5, Q6",TO-92_Inline_Wide,6,2N3904,
"R1, R2, R3, R31, R32, R4, R5, R6",R_Axial_DIN0207_L6.3mm_D2.5mm_P7.62mm_Horizontal,8,4.7k,
"R11, R12, R13, R14, R15, R16",R_Axial_DIN0207_L6.3mm_D2.5mm_P7.62mm_Horizontal,6,100k,
"R21, R22, R23, R24, R25, R26",R_Axial_DIN0207_L6.3mm_D2.5mm_P7.62mm_Horizontal,6,10k,
U1,WT32-ETH01_Socket_FaceDown,1,WT32-ETH01,
U2,Converter_DCDC_TRACO_TSR-1_THT,1,TSR 1-2450,

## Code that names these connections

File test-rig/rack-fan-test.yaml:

# Rack fan controller - TEST RIG firmware (WT32-ETH01 face up on a breadboard,
# 2 fan channels moved by jumper wires). Wiring and procedure: README.md.
#
# Drives all 6 PWM pins of the main board and counts all 8 tach-capable inputs
# (the 6 TACH pins plus the 2 1-Wire pins), so every pin can be checked by
# moving a fan's PWM wire / tach wire from pin to pin.
# Names carry the WT32 header pin number and the GPIO, e.g. "PWM1 pin26 IO1".

substitutions:
  friendly_name: "Rack Fan Test"

esphome:
  name: rack-fan-test
  # The LEDC outputs start at level 0, which with inverted: true switches the
  # transistors on and stops the fans: go to 100% as soon as they exist.
  on_boot:
    priority: 700
    then:
      - lambda: |-
          for (auto *pwm : {id(pwm_1), id(pwm_2), id(pwm_3), id(pwm_4), id(pwm_5), id(pwm_6)})
            pwm->set_level(1.0f);

esp32:
  board: wt32-eth01
  framework:
    type: esp-idf
    sdkconfig_options:
      # GPIO1 (U0TXD) is PWM1: keep ESP-IDF's own messages off it
      CONFIG_ESP_CONSOLE_NONE: y
      CONFIG_BOOTLOADER_LOG_LEVEL_NONE: y

logger:
  level: DEBUG
  # GPIO1/GPIO3 (UART0) are PWM1 and TACH1
  baud_rate: 0

api:

ota:
  - platform: esphome

ethernet:
  type: LAN8720
  mdc_pin: GPIO23
  mdio_pin: GPIO18
  clk:
    pin: GPIO0
    mode: CLK_EXT_IN
  phy_addr: 1
  power_pin: GPIO16

web_server:
  port: 80

#########################
# PWM OUTPUTS (same pins as the main board)
# Each drives a 2N3904 open collector on the fan's PWM wire, so the level is
# inverted: GPIO low = transistor off = fan 100%.

output:
  - platform: ledc
    id: pwm_1
    pin: GPIO1                       # WT32 pin 26
    inverted: true
    frequency: 25000 Hz
    zero_means_zero: true
  - platform: ledc
    id: pwm_2
    pin:
      number: GPIO12                 # WT32 pin 18 (strapping: kept low by the 100k)
      ignore_strapping_warning: true
    inverted: true
    frequency: 25000 Hz
    zero_means_zero: true
  - platform: ledc
    id: pwm_3
    pin: GPIO4                       # WT32 pin 16
    inverted: true
    frequency: 25000 Hz
    zero_means_zero: true
  - platform: ledc
    id: pwm_4
    pin:
      number: GPIO2                  # WT32 pin 15 (strapping: kept low by the 100k)
      ignore_strapping_warning: true
    inverted: true
    frequency: 25000 Hz
    zero_means_zero: true
  - platform: ledc
    id: pwm_5
    pin: GPIO32                      # WT32 pin 5
    inverted: true
    frequency: 25000 Hz
    zero_means_zero: true
  - platform: ledc
    id: pwm_6
    pin: GPIO33                      # WT32 pin 6
    inverted: true
    frequency: 25000 Hz
    zero_means_zero: true

# One duty slider per PWM pin, plus one for all of them (0-100%)
number:
  - platform: template
    id: duty_1
    name: "PWM1 pin26 IO1 duty"
    unit_of_measurement: "%"
    min_value: 0
    max_value: 100
    step: 5
    initial_value: 100
    optimistic: true
    set_action:
      - lambda: id(pwm_1).set_level(x / 100.0f);
  - platform: template
    id: duty_2
    name: "PWM2 pin18 IO12 duty"
    unit_of_measurement: "%"
    min_value: 0
    max_value: 100
    step: 5
    initial_value: 100
    optimistic: true
    set_action:
      - lambda: id(pwm_2).set_level(x / 100.0f);
  - platform: template
    id: duty_3
    name: "PWM3 pin16 IO4 duty"
    unit_of_measurement: "%"
    min_value: 0
    max_value: 100
    step: 5
    initial_value: 100
    optimistic: true
    set_action:
      - lambda: id(pwm_3).set_level(x / 100.0f);
  - platform: template
    id: duty_4
    name: "PWM4 pin15 IO2 duty"
    unit_of_measurement: "%"
    min_value: 0
    max_value: 100
    step: 5
    initial_value: 100
    optimistic: true
    set_action:
      - lambda: id(pwm_4).set_level(x / 100.0f);
  - platform: template
    id: duty_5
    name: "PWM5 pin5 IO32 duty"
    unit_of_measurement: "%"
    min_value: 0
    max_value: 100
    step: 5
    initial_value: 100
    optimistic: true
    set_action:
      - lambda: id(pwm_5).set_level(x / 100.0f);
  - platform: template
    id: duty_6
    name: "PWM6 pin6 IO33 duty"
    unit_of_measurement: "%"
    min_value: 0
    max_value: 100
    step: 5
    initial_value: 100
    optimistic: true
    set_action:
      - lambda: id(pwm_6).set_level(x / 100.0f);
  - platform: template
    id: duty_all
    name: "All PWM duty"
    unit_of_measurement: "%"
    min_value: 0
    max_value: 100
    step: 5
    initial_value: 100
    optimistic: true
    set_action:
      - lambda: |-
          for (auto *n : {id(duty_1), id(duty_2), id(duty_3), id(duty_4), id(duty_5), id(duty_6)}) {
            auto call = n->make_call();
            call.set_value(x);
            call.perform();
          }

#########################
# TACH INPUTS: 8 hardware pulse counters (the ESP32 has exactly 8)
# The 10k pull-up to 3.3 V sits on the test channel, so the pin it is moved to
# needs no pull-up of its own (35/36/39 have none).

sensor:
  - platform: pulse_counter
    name: "TACH1 pin25 IO3 rpm"
    pin:
      number: GPIO3
      mode: { input: true, pullup: true }
    internal_filter: 13us
    update_interval: 2s
    unit_of_measurement: "RPM"
    accuracy_decimals: 0
    filters: [multiply: 0.5]          # 2 pulses per revolution
  - platform: pulse_counter
    name: "TACH2 pin22 IO39 rpm"
    pin:
      number: GPIO39
      mode: { input: true, pullup: false }
    internal_filter: 13us
    update_interval: 2s
    unit_of_measurement: "RPM"
    accuracy_decimals: 0
    filters: [multiply: 0.5]
  - platform: pulse_counter
    name: "TACH3 pin21 IO36 rpm"
    pin:
      number: GPIO36
      mode: { input: true, pullup: false }
    internal_filter: 13us
    update_interval: 2s
    unit_of_measurement: "RPM"
    accuracy_decimals: 0
    filters: [multiply: 0.5]
  - platform: pulse_counter
    name: "TACH4 pin20 IO15 rpm"
    pin:
      number: GPIO15
      ignore_strapping_warning: true  # high at boot = default
      mode: { input: true, pullup: true }
    internal_filter: 13us
    update_interval: 2s
    unit_of_measurement: "RPM"
    accuracy_decimals: 0
    filters: [multiply: 0.5]
  - platform: pulse_counter
    name: "TACH5 pin19 IO14 rpm"
    pin:
      number: GPIO14
      mode: { input: true, pullup: true }
    internal_filter: 13us
    update_interval: 2s
    unit_of_measurement: "RPM"
    accuracy_decimals: 0
    filters: [multiply: 0.5]
  - platform: pulse_counter
    name: "TACH6 pin17 IO35 rpm"
    pin:
      number: GPIO35
      mode: { input: true, pullup: false }
    internal_filter: 13us
    update_interval: 2s
    unit_of_measurement: "RPM"
    accuracy_decimals: 0
    filters: [multiply: 0.5]
  # the two 1-Wire pins of the main board, used here as tach inputs
  - platform: pulse_counter
    name: "ONEWIRE_A pin7 IO5 rpm"
    pin:
      number: GPIO5
      ignore_strapping_warning: true  # high at boot = default
      mode: { input: true, pullup: true }
    internal_filter: 13us
    update_interval: 2s
    unit_of_measurement: "RPM"
    accuracy_decimals: 0
    filters: [multiply: 0.5]
  - platform: pulse_counter
    name: "ONEWIRE_B pin8 IO17 rpm"
    pin:
      number: GPIO17
      mode: { input: true, pullup: true }
    internal_filter: 13us
    update_interval: 2s
    unit_of_measurement: "RPM"
    accuracy_decimals: 0
    filters: [multiply: 0.5]

  - platform: uptime
    name: "${friendly_name} Uptime"
    update_interval: 60s

text_sensor:
  - platform: ethernet_info
    ip_address:
      name: "${friendly_name} IP Address"
  - platform: version
    name: "${friendly_name} ESPHome Version"
    hide_timestamp: true

# Sweep all six PWM pins 100 -> 75 -> 50 -> 25 -> 0 -> 100 %, 10 s per step
script:
  - id: sweep
    mode: restart
    then:
      - number.set: { id: duty_all, value: 100 }
      - delay: 10s
      - number.set: { id: duty_all, value: 75 }
      - delay: 10s
      - number.set: { id: duty_all, value: 50 }
      - delay: 10s
      - number.set: { id: duty_all, value: 25 }
      - delay: 10s
      - number.set: { id: duty_all, value: 0 }
      - delay: 10s
      - number.set: { id: duty_all, value: 100 }

button:
  - platform: template
    name: "Sweep all PWM"
    on_press:
      - script.execute: sweep
  - platform: restart
    name: "${friendly_name} Restart"

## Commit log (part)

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2023-11-16 changed namr of the component
2023-11-19 Several fixes
    - removed trail whitespaces
    - changed the code from DHT11 to DHT20 (and therefore i2c)
    - changed the GPIOs for the fan
2023-11-19 Commented dht warn level log, added quotes to names
2023-11-19 Added update_interval to pulse_counter, otherwise 60s
2023-11-19 Added include directory for SHT20
2023-11-19 Changed min speed to 0%, max speed to 100%
2023-11-19 Replaced hardened "Console Fan", fixed $friendly_name
    - the iteration of "Console Fan" has been moved to ${friendly_name}
    - the iteration of $friendly_name has been moved to ${friendly_name}
2023-11-19 Removed DHT11, quoted text with unicode
2023-11-20 Stable release v1.0
    - changed the friendly name
    - changed the id names
    - moved the sht20 library to have a configurable delay
    - added the missing component of sht20 to avoid unnamed devices
    - moved the component logging to error to avoid the 20-20ms warning
2025-05-14 added web server
2026-02-08 Fixed pinout, added comments
